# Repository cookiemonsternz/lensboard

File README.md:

# Lens Board

Lens Board is a custom mechanical keyboard, with a modified 1800's layout, more physical input methods (sliders, scrolly wheel, touchscreen) and an inbuilt, *physical* audio visualizer.

#### The Why

My inspiration for this project was my [Hackpad](https://hackpad.hackclub.com/) project, which I had a ton of fun designing and building. I wanted to make another thing to do with keyboards, and this was a great opportunity to do so.

In terms of the actual design choices of the keyboard, I'm a massive fan of analog / physical inputs and outputs. As a musician and LD, I like faders, so a few of those were an obvious choice. 

I decided to add a music visualizer because its just something I'm passionate about, putting some form of visual representation to sound. I do lighting for this reason, and I made my [music visualizer](https://cookiemonsternz.github.io/music-visualiser/) for high seas also because of this.

Anyways, here are some shots of my project :)

## BOM

For a nicer formatted bom, visit this [google sheet](https://docs.google.com/spreadsheets/d/1ZwZEnQPNZCf3j8q_c9diwTeRiC4rXLwVUGGG0oGG0jM/edit).

### Daughterboard

 Item | Part Name | Quantity | Source | Link | Unit Cost | Total Cost | Notes 
---|---|---|---|---|---|---|---
 U1 | RP2040 | 1 | JLCPCB Parts | https://jlcpcb.com/partdetail/RaspberryPi-RP2040/C2040 | 1.12 | 1.12 |  
 U2 | Voltage Regulator | 1 | JLCPCB Parts | https://jlcpcb.com/partdetail/bl_shanghai_belling-BL111733CX/C5400 | 0.05 | 0.05 | You can also use C26537, but its a bit more expensive 
 U3 | Flash Mem. | 1 | JLCPCB Parts | https://jlcpcb.com/partdetail/WinbondElec-W25Q128JVSIQ/C97521 | 0.74 | 0.74 |  
 U4 | Crystal Oscillator | 1 | JLCPCB Parts | https://jlcpcb.com/partdetail/AbraconLlc-ABM8_272T3/C20625731 | 0.36 | 0.36 |  
 U5, U6 | IO Expander | 2 | JLCPCB Parts | https://jlcpcb.com/partdetail/MicrochipTech-MCP23017T_EML/C629439 | 1.55 | 3.1 |  
 J1 | DC Barrel Jack | 1 | JLCPCB Parts | https://jlcpcb.com/partdetail/ShouHan-DC005/C431533 | 0.05 | 0.05 |  
 J2 | USB C Conn | 1 | JLCPCB Parts | https://jlcpcb.com/partdetail/Korean_HropartsElec-TYPE_C_31_M12/C165948 | 0.17 | 0.17 |  
 J3 | 2x30 Pin Header | 1 | Aliexpress | https://www.aliexpress.com/item/32214180690.html?spm=a2g0o.productlist.main.11.62007aa28osNlK&algo_pvid=4aeb8a1d-9196-4dce-9fd8-8f74cdbfb503&algo_exp_id=4aeb8a1d-9196-4dce-9fd8-8f74cdbfb503-10&pdp_ext_f=%7B%22order%22%3A%2212%22%2C%22eval%22%3A%221%22%7D&pdp_npi=4%40dis%21USD%210.76%210.76%21%21%210.76%210.76%21%402103246617503783498077610ef0cd%2112000023678787662%21sea%21NZ%212895682434%21X&curPageLogUid=gqU9QpHzRo8G&utparam-url=scene%3Asearch%7Cquery_from%3A | 0.15 | 0.15 |  
 R1, R2 | 1kΩ Resistor | 2 | JLCPCB Parts | https://jlcpcb.com/partdetail/12256-0402WGF1001TCE/C11702 | 0.01 | 0.02 |  
 R3, R4 | 27.4Ω Resistor | 2 | JLCPCB Parts | https://jlcpcb.com/partdetail/25848-0402WGF330JTCE/C25105 | 0.01 | 0.02 | Using 33Ω resistors instead here, technically not to spec, but will almost certainly still work 
 R5, R6 | 5.1kΩ Resistor | 2 | JLCPCB Parts | https://jlcpcb.com/partdetail/26648-0402WGF5101TCE/C25905 | 0.01 | 0.02 |  
 R7, R8 | 4.7kΩ Resistor | 2 | JLCPCB Parts | https://jlcpcb.com/partdetail/26643-0402WGF4701TCE/C25900 | 0.01 | 0.02 |  
 C1, C2 | 10uF Capacitor | 2 | JLCPCB Parts | https://jlcpcb.com/partdetail/20411-CL10A106KP8NNNC/C19702 | 0.01 | 0.02 | 0603, all other smd r and c are 0402 
 C3, C4, C5, C6, C7, C8, C9, C12, C13, C14 | 100nF Capacitor | 10 | JLCPCB Parts | https://jlcpcb.com/partdetail/1877-CL05B104KO5NNNC/C1525 | 0.01 | 0.1 |  
 C10, C11 | 1uF Capacitor | 2 | JLCPCB Parts | https://jlcpcb.com/partdetail/16531-CL10A105KB8NNNC/C15849 | 0.01 | 0.02 | 0603, all other smd r and c are 0402 
 C15, C16 | 15pF Capacitor | 2 | JLCPCB Parts | https://jlcpcb.com/partdetail/1900-0402CG150J500NT/C1548 | 0.01 | 0.02 |  
 BOARD | PCB Board | 1 | JLCPCB | NA | 0.8 | 0.8 | Excl. PCBA, default settings (1.6mm fr4), this is assuming 5 ordered, and this is the cost of 1 
 PCBA | PCB Assembly |  |  |  | 21.01 | 21.01 | This includes the cost of parts, so the cost of jlcpcb parts has been excluded from the total cost, again this is the cost for 1, but min order is 2 
 Total Cost |  |  |  |  |  |  |  
 Single Board |  |  |  |  |  | 21.96 |  
 Min Order (JLCPCB) |  |  |  |  |  | 46.17 |  

### Main Board

 Item | Part Name | Quantity | Source | Link | Unit Cost | Total Cost | Notes 
---|---|---|---|---|---|---|---
 BOARD | PCB Board | 1 | JLCPCB | NA | 5.38 | 5.38 | default settings (1.6mm fr4), this is assuming 5 ordered, and this is the cost of 1 
 J1 | 2x30 Pin Header | 1 | Aliexpress | https://www.aliexpress.com/item/32214180690.html?spm=a2g0o.productlist.main.11.62007aa28osNlK&algo_pvid=4aeb8a1d-9196-4dce-9fd8-8f74cdbfb503&algo_exp_id=4aeb8a1d-9196-4dce-9fd8-8f74cdbfb503-10&pdp_ext_f=%7B%22order%22%3A%2212%22%2C%22eval%22%3A%221%22%7D&pdp_npi=4%40dis%21USD%210.76%210.76%21%21%210.76%210.76%21%402103246617503783498077610ef0cd%2112000023678787662%21sea%21NZ%212895682434%21X&curPageLogUid=gqU9QpHzRo8G&utparam-url=scene%3Asearch%7Cquery_from%3A | 0.15 | 0.15 |  
 R109, R110 | Slide Potentiometer | 2 | Mouser | https://nz.mouser.com/ProductDetail/Bourns/PTA3043-2010CIB103?qs=QARuOjD9jaF0iQfIvhCxcQ%3D%3D | 1.4 | 2.8 | This is a hard part to find on aliexpress, I'm going to adapt my pcb to the ones I currently have, but be very careful how you choose this part 
 U7 | LED Transistor | 1 | Aliexpress | https://www.aliexpress.com/item/32966478417.html | 0.04 | 0.81 | Again, find one with the same footprint and similar specs 
 SW101 | Rotary Encoder | 1 | Aliexpress | https://www.aliexpress.com/item/1005008562951299.html?spm=a2g0o.productlist.main.2.694610473NnPbb&algo_pvid=771bf3ee-44f4-41f8-acc5-89f292c9e139&algo_exp_id=771bf3ee-44f4-41f8-acc5-89f292c9e139-1&pdp_ext_f=%7B%22order%22%3A%22-1%22%2C%22eval%22%3A%221%22%7D&pdp_npi=4%40dis%21USD%213.08%212.74%21%21%2122.00%2119.58%21%402103146c17504851750608347e0951%2112000045732012789%21sea%21NZ%212895682434%21X&curPageLogUid=0EsiDwbyuniA&utparam-url=scene%3Asearch%7Cquery_from%3A | 0.27 | 2.74 | Same as above 
 SW1 - SW 100 | Keyswitches | 100 | Aliexpress | https://www.aliexpress.com/item/1005009054805658.html | 0.23 | 22.81 | Assuming ordering 100 
 D1 - D100 | Key Diodes | 100 | Aliexpress | https://www.aliexpress.com/item/1005005460442161.html | 0.01 | 0.61 | Assuming ordering 100 
 D101 - D200 | Backlight LEDs | 100 | Aliexpress | https://www.aliexpress.com/item/1005005226854182.html | 0.01 | 1.45 | Assuming ordering 100 
 R9 - R108 | LED Resistor | 100 | Aliexpress | https://www.aliexpress.com/item/1005003297851656.html | 0.02 | 1.7 | Assuming ordering 100 
 J3, J4 | Touchscreen | 1 | Aliexpress | https://www.aliexpress.com/item/1005004055677573.html | 6.95 | 6.95 | With touch 
 M1 - M10 | Servo | 10 | Aliexpress | https://www.aliexpress.com/item/1005008626768357.html | 1.8 | 18.29 | 10x 180° MG90s 
 Total Cost |  |  |  |  |  |  |  
 Single Board |  |  |  |  |  | 63.69 |  
 Min Order (JLCPCB) |  |  |  |  |  | 103.11 | Only min order for jlcpcb, not for j1, all others already are min order. 

### Full Keyboard

 Item | Part Name | Quantity | Source | Link | Unit Cost | Total Cost | Notes 
---|---|---|---|---|---|---|---
 MAIN | Main Board | 1 | Various | NA | 81.59 | 103.11 | Total cost is different because of minimum orders 
 SUB | Daughter Board | 1 | Various | NA | 21.96 | 46.17 | Same as above, see individual boms 
 CASEB |  | 1 | 3d printing | NA | NA | NA | 3d printing this myself, not enough filament to compensate 
 CASET |  | 1 | 3d printing | NA | NA | NA | 3d printing this myself, not enough filament to compensate 
 PLATE |  | 1 | Laser cut / cnc | NA | NA | NA | 3d printing this myself, not enough filament to compensate 
 INS | Heatset inserts | 100 | Aliexpress | https://www.aliexpress.com/item/1005006838108683.html | 0.03 | 2.72 | OD 3.2, L3, M2, This is for 100, but couldn't find any smaller amounts 
 STA | Standoffs | 20 | Aliexpress | https://www.aliexpress.com/item/1005002952338852.html | 0.13 | 2.69 | M2, 12mm, 20 pc 
 KC | Keycaps | 100 | Aliexpress | https://www.aliexpress.com/item/1005008486798694.html | 0.05 | 5.44 |  
 Total Cost |  |  |  |  |  |  |  
 Single Board |  |  |  |  |  | 114.4 |  
 Total Cost (excl. Shipping) |  |  |  |  |  | 160.13 |  
 Total Cost (incl. Shipping) |  |  |  |  |  | 168.94 | Aliexpress parts = 70.60, JLCPCB = 98.34

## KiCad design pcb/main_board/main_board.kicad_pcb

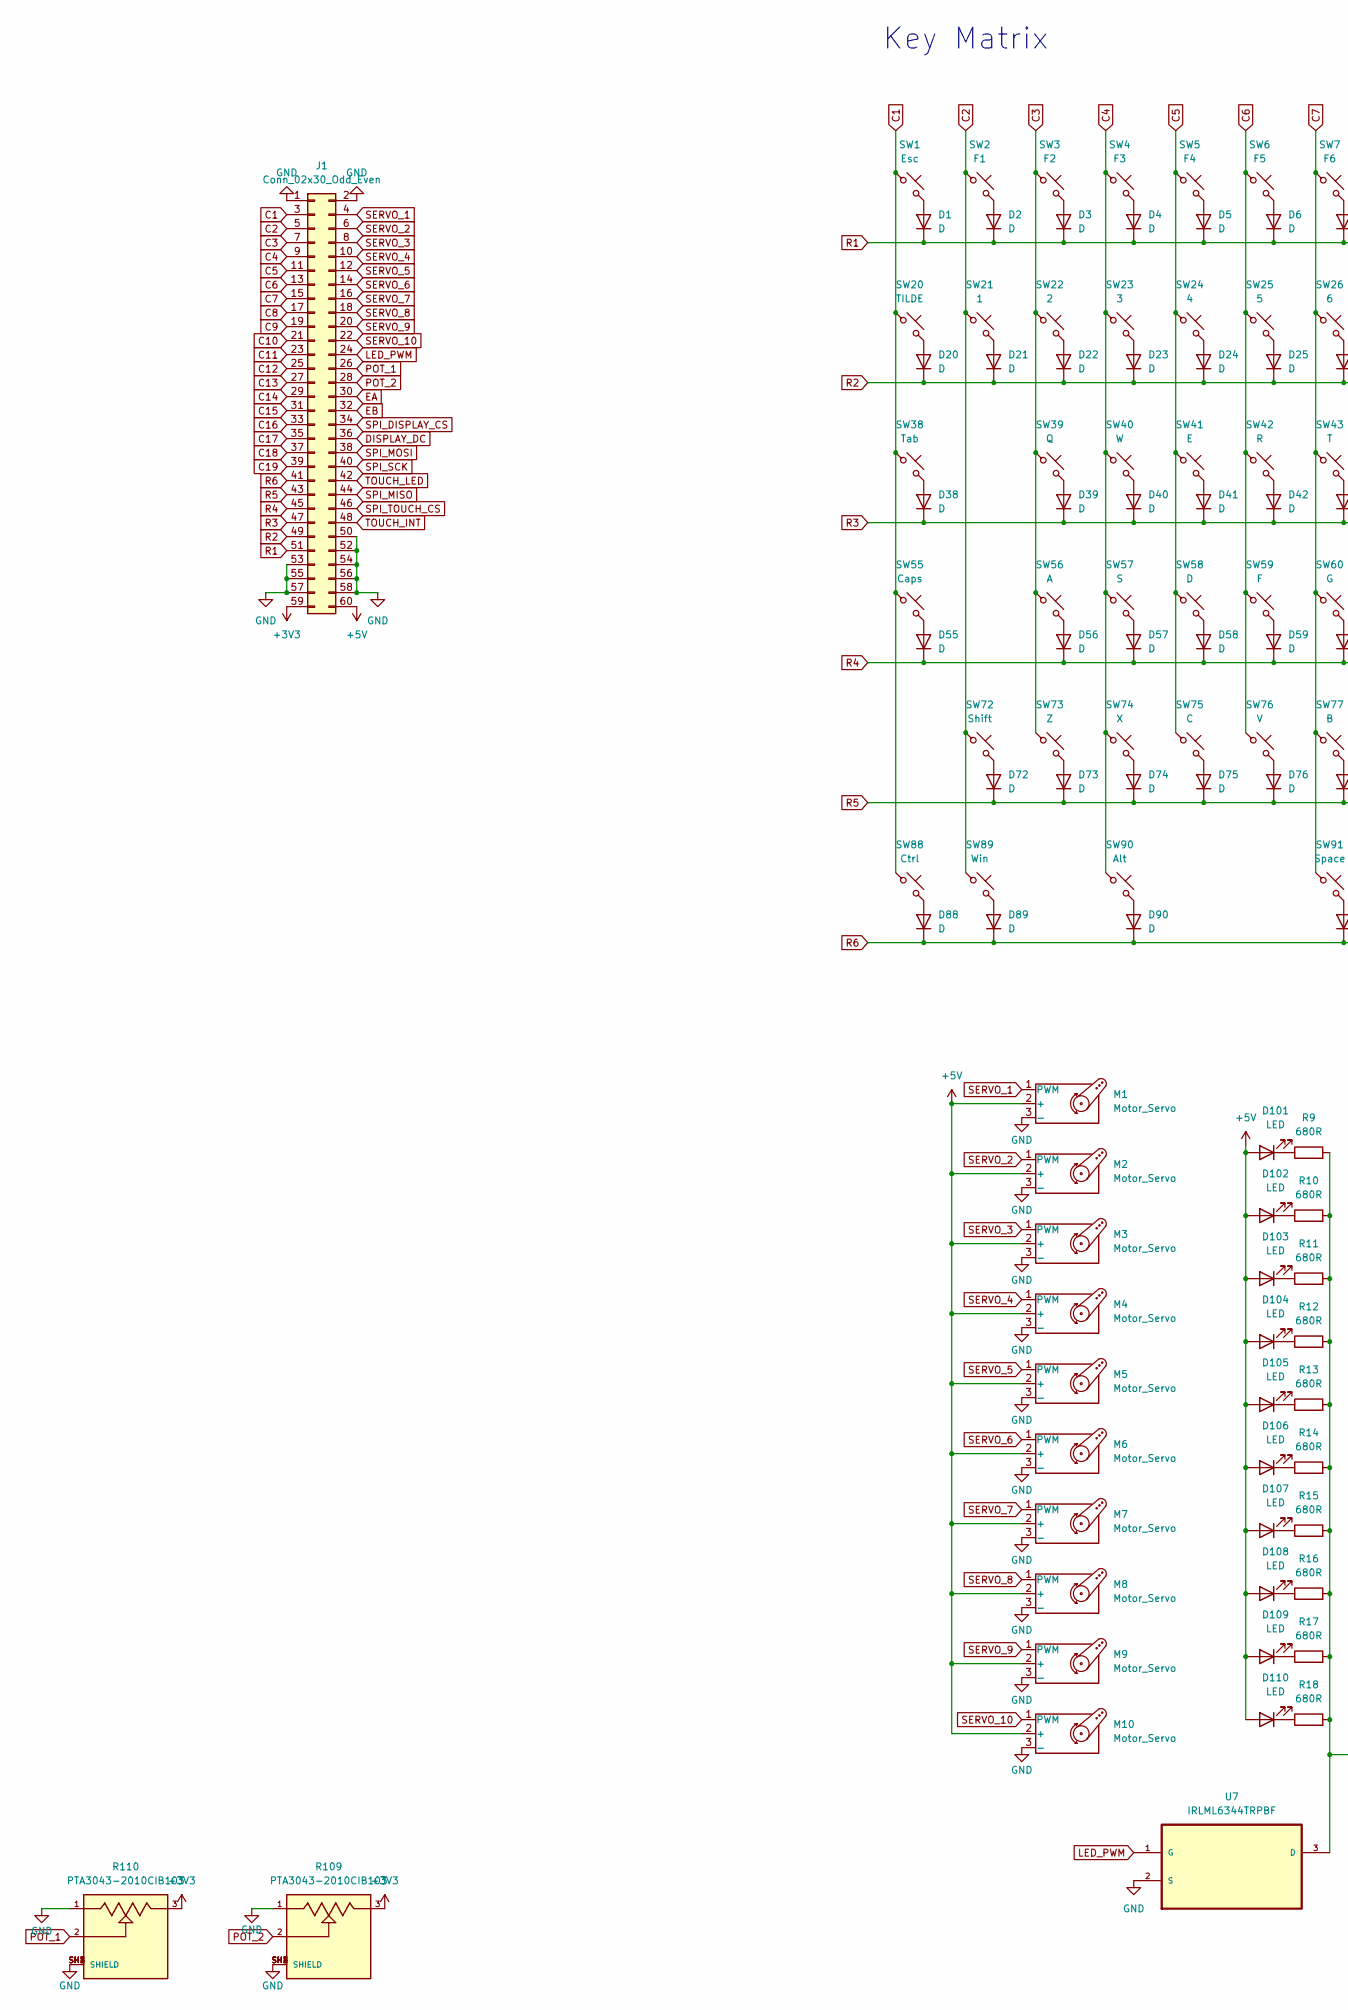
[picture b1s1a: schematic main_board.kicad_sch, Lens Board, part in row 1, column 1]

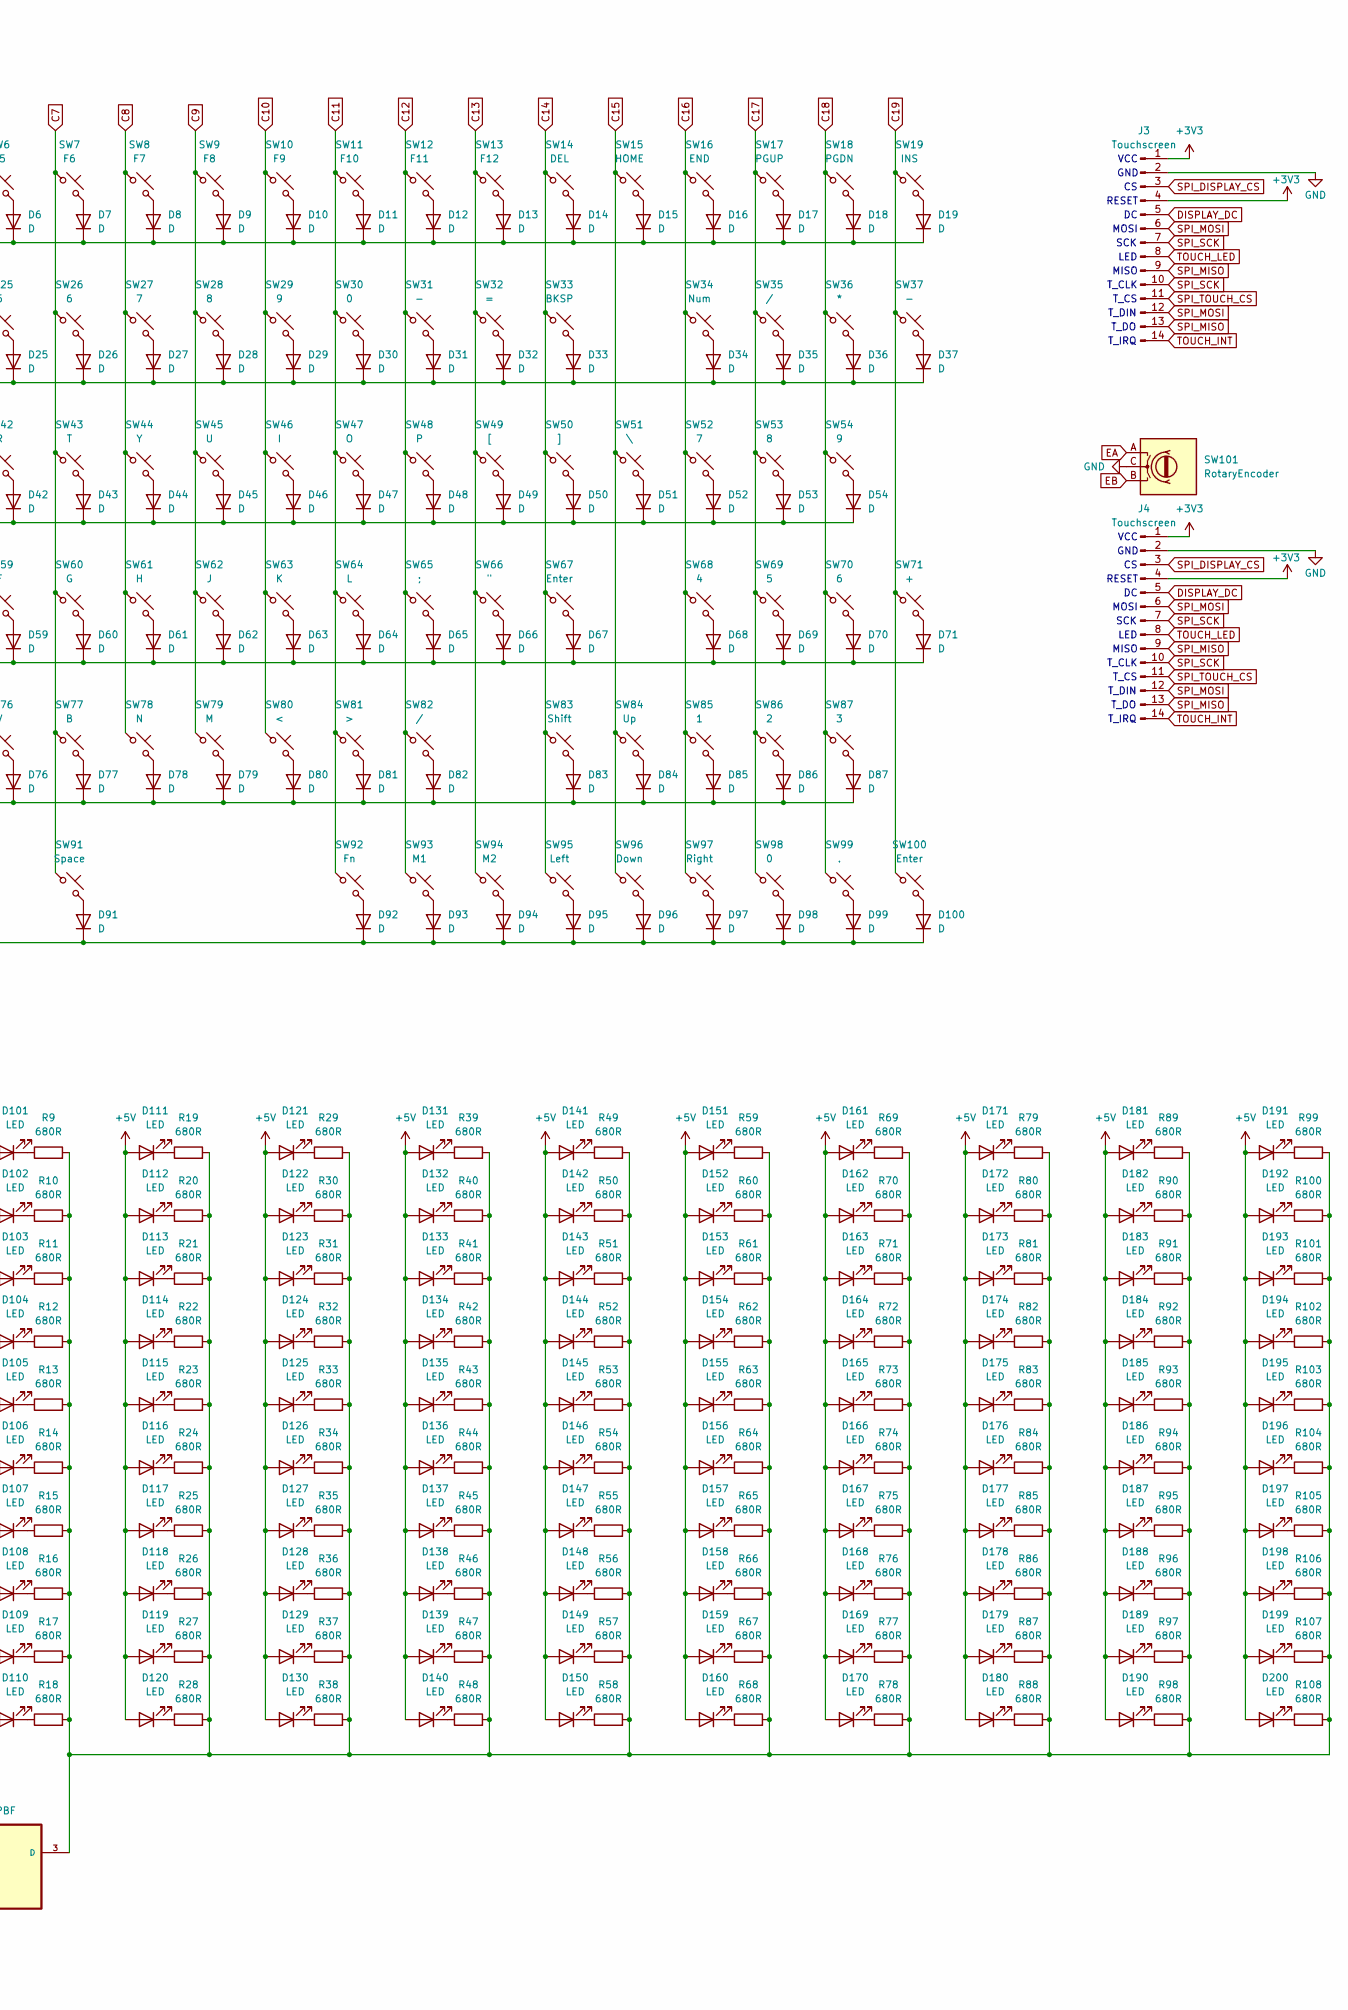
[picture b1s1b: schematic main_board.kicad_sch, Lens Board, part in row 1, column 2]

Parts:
D1, D2, D3, D4, D5, D6, D7, D8, D9, D10, D11, D12, D13, D14, D15, D16, D17, D18, D19, D20, D21, D22, D23, D24, D25, D26, D27, D28, D29, D30, D31, D32, D33, D34, D35, D36, D37, D38, D39, D40, D41, D42, D43, D44, D45, D46, D47, D48, D49, D50, D51, D52, D53, D54, D55, D56, D57, D58, D59, D60, D61, D62, D63, D64, D65, D66, D67, D68, D69, D70, D71, D72, D73, D74, D75, D76, D77, D78, D79, D80, D81, D82, D83, D84, D85, D86, D87, D88, D89, D90, D91, D92, D93, D94, D95, D96, D97, D98, D99, D100: D; D_SOD-323
D101, D102, D103, D104, D105, D106, D107, D108, D109, D110, D111, D112, D113, D114, D115, D116, D117, D118, D119, D120, D121, D122, D123, D124, D125, D126, D127, D128, D129, D130, D131, D132, D133, D134, D135, D136, D137, D138, D139, D140, D141, D142, D143, D144, D145, D146, D147, D148, D149, D150, D151, D152, D153, D154, D155, D156, D157, D158, D159, D160, D161, D162, D163, D164, D165, D166, D167, D168, D169, D170, D171, D172, D173, D174, D175, D176, D177, D178, D179, D180, D181, D182, D183, D184, D185, D186, D187, D188, D189, D190, D191, D192, D193, D194, D195, D196, D197, D198, D199, D200: LED; LED_0603_1608Metric
J1: Conn_02x30_Odd_Even; PinHeader_2x30_P1.27mm_Vertical
J3, J4: Touchscreen; PinHeader_1x14_P2.54mm_Vertical
M1, M2, M3, M4, M5, M6, M7, M8, M9, M10: Motor_Servo; PinHeader_1x03_P2.54mm_Vertical
R9, R10, R11, R12, R13, R14, R15, R16, R17, R18, R19, R20, R21, R22, R23, R24, R25, R26, R27, R28, R29, R30, R31, R32, R33, R34, R35, R36, R37, R38, R39, R40, R41, R42, R43, R44, R45, R46, R47, R48, R49, R50, R51, R52, R53, R54, R55, R56, R57, R58, R59, R60, R61, R62, R63, R64, R65, R66, R67, R68, R69, R70, R71, R72, R73, R74, R75, R76, R77, R78, R79, R80, R81, R82, R83, R84, R85, R86, R87, R88, R89, R90, R91, R92, R93, R94, R95, R96, R97, R98, R99, R100, R101, R102, R103, R104, R105, R106, R107, R108: 680R; R_0402_1005Metric
R109, R110: PTA3043-2010CIB103; TRIM_PTA3043-2010CIB103; PARTREV 04/21; DigiKey_Part_Number PTA3043-2010CIB103-ND
SW1: Esc; MX-Hotswap-1U
SW2: F1; MX-Hotswap-1U
SW3: F2; MX-Hotswap-1U
SW4: F3; MX-Hotswap-1U
SW5: F4; MX-Hotswap-1U
SW6: F5; MX-Hotswap-1U
SW7: F6; MX-Hotswap-1U
SW8: F7; MX-Hotswap-1U
SW9: F8; MX-Hotswap-1U
SW10: F9; MX-Hotswap-1U
SW11: F10; MX-Hotswap-1U
SW12: F11; MX-Hotswap-1U
SW13: F12; MX-Hotswap-1U
SW14: DEL; MX-Hotswap-1U
SW15: HOME; MX-Hotswap-1U
SW16: END; MX-Hotswap-1U
SW17: PGUP; MX-Hotswap-1U
SW18: PGDN; MX-Hotswap-1U
SW19: INS; MX-Hotswap-1U
SW20: TILDE; MX-Hotswap-1U
SW21, SW85: 1; MX-Hotswap-1U
SW22, SW86: 2; MX-Hotswap-1U
SW23, SW87: 3; MX-Hotswap-1U
SW24, SW68: 4; MX-Hotswap-1U
SW25, SW69: 5; MX-Hotswap-1U
SW26, SW70: 6; MX-Hotswap-1U
SW27, SW52: 7; MX-Hotswap-1U
SW28, SW53: 8; MX-Hotswap-1U
SW29, SW54: 9; MX-Hotswap-1U
SW30, SW98: 0; MX-Hotswap-1U
SW31, SW37: -; MX-Hotswap-1U
SW32: =; MX-Hotswap-1U
SW33: BKSP; MX-Hotswap-2U
SW34: Num; MX-Hotswap-1U
SW35, SW82: /; MX-Hotswap-1U
SW36: *; MX-Hotswap-1U
SW38: Tab; MX-Hotswap-1.5U
SW39: Q; MX-Hotswap-1U
SW40: W; MX-Hotswap-1U
SW41: E; MX-Hotswap-1U
SW42: R; MX-Hotswap-1U
SW43: T; MX-Hotswap-1U
SW44: Y; MX-Hotswap-1U
SW45: U; MX-Hotswap-1U
SW46: I; MX-Hotswap-1U
SW47: O; MX-Hotswap-1U
SW48: P; MX-Hotswap-1U
SW49: [; MX-Hotswap-1U
SW50: ]; MX-Hotswap-1U
SW51: \; MX-Hotswap-1.5U
SW55: Caps; MX-Hotswap-1.75U
SW56: A; MX-Hotswap-1U
SW57: S; MX-Hotswap-1U
SW58: D; MX-Hotswap-1U
SW59: F; MX-Hotswap-1U
SW60: G; MX-Hotswap-1U
SW61: H; MX-Hotswap-1U
SW62: J; MX-Hotswap-1U
SW63: K; MX-Hotswap-1U
SW64: L; MX-Hotswap-1U
SW65: ;; MX-Hotswap-1U
SW66: "; MX-Hotswap-1U
SW67: Enter; MX-Hotswap-2.25U
SW71: +; MX-Hotswap-2U-Vertical
SW72: Shift; MX-Hotswap-2.25U
SW73: Z; MX-Hotswap-1U
SW74: X; MX-Hotswap-1U
SW75: C; MX-Hotswap-1U
SW76: V; MX-Hotswap-1U
SW77: B; MX-Hotswap-1U
SW78: N; MX-Hotswap-1U
SW79: M; MX-Hotswap-1U
SW80: <; MX-Hotswap-1U
SW81: >; MX-Hotswap-1U
SW83: Shift; MX-Hotswap-1.75U
SW84: Up; MX-Hotswap-1U
SW88: Ctrl; MX-Hotswap-1.25U
SW89: Win; MX-Hotswap-1.25U
SW90: Alt; MX-Hotswap-1.25U
SW91: Space; MX-Hotswap-6.25U
SW92: Fn; MX-Hotswap-1U
SW93: M1; MX-Hotswap-1U
SW94: M2; MX-Hotswap-1U
SW95: Left; MX-Hotswap-1U
SW96: Down; MX-Hotswap-1U
SW97: Right; MX-Hotswap-1U
SW99: .; MX-Hotswap-1U
SW100: Enter; MX-Hotswap-2U-Vertical
SW101: RotaryEncoder; TRIM_EC10E1220501
U7: IRLML6344TRPBF; SOT95P240X112-3N; MPN IRLML6344TRPBF

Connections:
+3V3: J1.59, J3.1, J3.4, J4.1, J4.4, R109.3, R110.3
+5V: D101.2 (A), D102.2 (A), D103.2 (A), D104.2 (A), D105.2 (A), D106.2 (A), D107.2 (A), D108.2 (A), D109.2 (A), D110.2 (A), D111.2 (A), D112.2 (A), D113.2 (A), D114.2 (A), D115.2 (A), D116.2 (A), D117.2 (A), D118.2 (A), D119.2 (A), D120.2 (A), D121.2 (A), D122.2 (A), D123.2 (A), D124.2 (A), D125.2 (A), D126.2 (A), D127.2 (A), D128.2 (A), D129.2 (A), D130.2 (A), D131.2 (A), D132.2 (A), D133.2 (A), D134.2 (A), D135.2 (A), D136.2 (A), D137.2 (A), D138.2 (A), D139.2 (A), D140.2 (A), D141.2 (A), D142.2 (A), D143.2 (A), D144.2 (A), D145.2 (A), D146.2 (A), D147.2 (A), D148.2 (A), D149.2 (A), D150.2 (A), D151.2 (A), D152.2 (A), D153.2 (A), D154.2 (A), D155.2 (A), D156.2 (A), D157.2 (A), D158.2 (A), D159.2 (A), D160.2 (A), D161.2 (A), D162.2 (A), D163.2 (A), D164.2 (A), D165.2 (A), D166.2 (A), D167.2 (A), D168.2 (A), D169.2 (A), D170.2 (A), D171.2 (A), D172.2 (A), D173.2 (A), D174.2 (A), D175.2 (A), D176.2 (A), D177.2 (A), D178.2 (A), D179.2 (A), D180.2 (A), D181.2 (A), D182.2 (A), D183.2 (A), D184.2 (A), D185.2 (A), D186.2 (A), D187.2 (A), D188.2 (A), D189.2 (A), D190.2 (A), D191.2 (A), D192.2 (A), D193.2 (A), D194.2 (A), D195.2 (A), D196.2 (A), D197.2 (A), D198.2 (A), D199.2 (A), D200.2 (A), J1.60, M1.2 (+), M2.2 (+), M3.2 (+), M4.2 (+), M5.2 (+), M6.2 (+), M7.2 (+), M8.2 (+), M9.2 (+), M10.2 (+)
C1: J1.3, SW1.1, SW20.1, SW38.1, SW55.1, SW88.1
C2: J1.5, SW2.1, SW21.1, SW72.1, SW89.1
C3: J1.7, SW3.1, SW22.1, SW39.1, SW56.1, SW73.1
C4: J1.9, SW4.1, SW23.1, SW40.1, SW57.1, SW74.1, SW90.1
C5: J1.11, SW5.1, SW24.1, SW41.1, SW58.1, SW75.1
C6: J1.13, SW6.1, SW25.1, SW42.1, SW59.1, SW76.1
C7: J1.15, SW7.1, SW26.1, SW43.1, SW60.1, SW77.1, SW91.1
C8: J1.17, SW8.1, SW27.1, SW44.1, SW61.1, SW78.1
C9: J1.19, SW9.1, SW28.1, SW45.1, SW62.1, SW79.1
C10: J1.21, SW10.1, SW29.1, SW46.1, SW63.1, SW80.1
C11: J1.23, SW11.1, SW30.1, SW47.1, SW64.1, SW81.1, SW92.1
C12: J1.25, SW12.1, SW31.1, SW48.1, SW65.1, SW82.1, SW93.1
C13: J1.27, SW13.1, SW32.1, SW49.1, SW66.1, SW94.1
C14: J1.29, SW14.1, SW33.1, SW50.1, SW67.1, SW83.1, SW95.1
C15: J1.31, SW15.1, SW51.1, SW84.1, SW96.1
C16: J1.33, SW16.1, SW34.1, SW52.1, SW68.1, SW85.1, SW97.1
C17: J1.35, SW17.1, SW35.1, SW53.1, SW69.1, SW86.1, SW98.1
C18: J1.37, SW18.1, SW36.1, SW54.1, SW70.1, SW87.1, SW99.1
C19: J1.39, SW19.1, SW37.1, SW71.1, SW100.1
DISPLAY_DC: J1.36, J3.5, J4.5
EA: J1.30, SW101.A
EB: J1.32, SW101.B
GND: J1.1, J1.2, J1.50, J1.52, J1.53, J1.54, J1.55, J1.56, J1.57, J1.58, J3.2, J4.2, M1.3 (-), M2.3 (-), M3.3 (-), M4.3 (-), M5.3 (-), M6.3 (-), M7.3 (-), M8.3 (-), M9.3 (-), M10.3 (-), R109.1, R109.SH1 (SHIELD), R109.SH2 (SHIELD), R109.SH3 (SHIELD), R109.SH4 (SHIELD), R110.1, R110.SH1 (SHIELD), R110.SH2 (SHIELD), R110.SH3 (SHIELD), R110.SH4 (SHIELD), SW101.C, U7.2 (S)
LED_PWM: J1.24, U7.1 (G)
unnamed: D1.2 (A), SW1.2
unnamed: D2.2 (A), SW2.2
unnamed: D3.2 (A), SW3.2
unnamed: D4.2 (A), SW4.2
unnamed: D5.2 (A), SW5.2
unnamed: D6.2 (A), SW6.2
unnamed: D7.2 (A), SW7.2
unnamed: D8.2 (A), SW8.2
unnamed: D9.2 (A), SW9.2
unnamed: D10.2 (A), SW10.2
unnamed: D11.2 (A), SW11.2
unnamed: D12.2 (A), SW12.2
unnamed: D13.2 (A), SW13.2
unnamed: D14.2 (A), SW14.2
unnamed: D15.2 (A), SW15.2
unnamed: D16.2 (A), SW16.2
unnamed: D17.2 (A), SW17.2
unnamed: D18.2 (A), SW18.2
unnamed: D19.2 (A), SW19.2
unnamed: D20.2 (A), SW20.2
unnamed: D21.2 (A), SW21.2
unnamed: D22.2 (A), SW22.2
unnamed: D23.2 (A), SW23.2
unnamed: D24.2 (A), SW24.2
unnamed: D25.2 (A), SW25.2
unnamed: D26.2 (A), SW26.2
unnamed: D27.2 (A), SW27.2
unnamed: D28.2 (A), SW28.2
unnamed: D29.2 (A), SW29.2
unnamed: D30.2 (A), SW30.2
unnamed: D31.2 (A), SW31.2
unnamed: D32.2 (A), SW32.2
unnamed: D33.2 (A), SW33.2
unnamed: D34.2 (A), SW34.2
unnamed: D35.2 (A), SW35.2
unnamed: D36.2 (A), SW36.2
unnamed: D37.2 (A), SW37.2
unnamed: D38.2 (A), SW38.2
unnamed: D39.2 (A), SW39.2
unnamed: D40.2 (A), SW40.2
unnamed: D41.2 (A), SW41.2
unnamed: D42.2 (A), SW42.2
unnamed: D43.2 (A), SW43.2
unnamed: D44.2 (A), SW44.2
unnamed: D45.2 (A), SW45.2
unnamed: D46.2 (A), SW46.2
unnamed: D47.2 (A), SW47.2
unnamed: D48.2 (A), SW48.2
unnamed: D49.2 (A), SW49.2
unnamed: D50.2 (A), SW50.2
unnamed: D51.2 (A), SW51.2
unnamed: D52.2 (A), SW52.2
unnamed: D53.2 (A), SW53.2
unnamed: D54.2 (A), SW54.2
unnamed: D55.2 (A), SW55.2
unnamed: D56.2 (A), SW56.2
unnamed: D57.2 (A), SW57.2
unnamed: D58.2 (A), SW58.2
unnamed: D59.2 (A), SW59.2
unnamed: D60.2 (A), SW60.2
unnamed: D61.2 (A), SW61.2
unnamed: D62.2 (A), SW62.2
unnamed: D63.2 (A), SW63.2
unnamed: D64.2 (A), SW64.2
unnamed: D65.2 (A), SW65.2
unnamed: D66.2 (A), SW66.2
unnamed: D67.2 (A), SW67.2
unnamed: D68.2 (A), SW68.2
unnamed: D69.2 (A), SW69.2
unnamed: D70.2 (A), SW70.2
unnamed: D71.2 (A), SW71.2
unnamed: D72.2 (A), SW72.2
unnamed: D73.2 (A), SW73.2
unnamed: D74.2 (A), SW74.2
unnamed: D75.2 (A), SW75.2
unnamed: D76.2 (A), SW76.2
unnamed: D77.2 (A), SW77.2
unnamed: D78.2 (A), SW78.2
unnamed: D79.2 (A), SW79.2
unnamed: D80.2 (A), SW80.2
unnamed: D81.2 (A), SW81.2
unnamed: D82.2 (A), SW82.2
unnamed: D83.2 (A), SW83.2
unnamed: D84.2 (A), SW84.2
unnamed: D85.2 (A), SW85.2
unnamed: D86.2 (A), SW86.2
unnamed: D87.2 (A), SW87.2
unnamed: D88.2 (A), SW88.2
unnamed: D89.2 (A), SW89.2
unnamed: D90.2 (A), SW90.2
unnamed: D91.2 (A), SW91.2
unnamed: D92.2 (A), SW92.2
unnamed: D93.2 (A), SW93.2
unnamed: D94.2 (A), SW94.2
unnamed: D95.2 (A), SW95.2
unnamed: D96.2 (A), SW96.2
unnamed: D97.2 (A), SW97.2
unnamed: D98.2 (A), SW98.2
unnamed: D99.2 (A), SW99.2
unnamed: D100.2 (A), SW100.2
unnamed: D101.1 (K), R9.1
unnamed: D102.1 (K), R10.1
unnamed: D103.1 (K), R11.1
unnamed: D104.1 (K), R12.1
unnamed: D105.1 (K), R13.1
unnamed: D106.1 (K), R14.1
unnamed: D107.1 (K), R15.1
unnamed: D108.1 (K), R16.1
unnamed: D109.1 (K), R17.1
unnamed: D110.1 (K), R18.1
unnamed: D111.1 (K), R19.1
unnamed: D112.1 (K), R20.1
unnamed: D113.1 (K), R21.1
unnamed: D114.1 (K), R22.1
unnamed: D115.1 (K), R23.1
unnamed: D116.1 (K), R24.1
unnamed: D117.1 (K), R25.1
unnamed: D118.1 (K), R26.1
unnamed: D119.1 (K), R27.1
unnamed: D120.1 (K), R28.1
unnamed: D121.1 (K), R29.1
unnamed: D122.1 (K), R30.1
unnamed: D123.1 (K), R31.1
unnamed: D124.1 (K), R32.1
unnamed: D125.1 (K), R33.1
unnamed: D126.1 (K), R34.1
unnamed: D127.1 (K), R35.1
unnamed: D128.1 (K), R36.1
unnamed: D129.1 (K), R37.1
unnamed: D130.1 (K), R38.1
unnamed: D131.1 (K), R39.1
unnamed: D132.1 (K), R40.1
unnamed: D133.1 (K), R41.1
unnamed: D134.1 (K), R42.1
unnamed: D135.1 (K), R43.1
unnamed: D136.1 (K), R44.1
unnamed: D137.1 (K), R45.1
unnamed: D138.1 (K), R46.1
unnamed: D139.1 (K), R47.1
unnamed: D140.1 (K), R48.1
unnamed: D141.1 (K), R49.1
unnamed: D142.1 (K), R50.1
unnamed: D143.1 (K), R51.1
unnamed: D144.1 (K), R52.1
unnamed: D145.1 (K), R53.1
unnamed: D146.1 (K), R54.1
unnamed: D147.1 (K), R55.1
unnamed: D148.1 (K), R56.1
unnamed: D149.1 (K), R57.1
unnamed: D150.1 (K), R58.1
unnamed: D151.1 (K), R59.1
unnamed: D152.1 (K), R60.1
unnamed: D153.1 (K), R61.1
unnamed: D154.1 (K), R62.1
unnamed: D155.1 (K), R63.1
unnamed: D156.1 (K), R64.1
unnamed: D157.1 (K), R65.1
unnamed: D158.1 (K), R66.1
unnamed: D159.1 (K), R67.1
unnamed: D160.1 (K), R68.1
unnamed: D161.1 (K), R69.1
unnamed: D162.1 (K), R70.1
unnamed: D163.1 (K), R71.1
unnamed: D164.1 (K), R72.1
unnamed: D165.1 (K), R73.1
unnamed: D166.1 (K), R74.1
unnamed: D167.1 (K), R75.1
unnamed: D168.1 (K), R76.1
unnamed: D169.1 (K), R77.1
unnamed: D170.1 (K), R78.1
unnamed: D171.1 (K), R79.1
unnamed: D172.1 (K), R80.1
unnamed: D173.1 (K), R81.1
unnamed: D174.1 (K), R82.1
unnamed: D175.1 (K), R83.1
unnamed: D176.1 (K), R84.1
unnamed: D177.1 (K), R85.1
unnamed: D178.1 (K), R86.1
unnamed: D179.1 (K), R87.1
unnamed: D180.1 (K), R88.1
unnamed: D181.1 (K), R89.1
unnamed: D182.1 (K), R90.1
unnamed: D183.1 (K), R91.1
unnamed: D184.1 (K), R92.1
unnamed: D185.1 (K), R93.1
unnamed: D186.1 (K), R94.1
unnamed: D187.1 (K), R95.1
unnamed: D188.1 (K), R96.1
unnamed: D189.1 (K), R97.1
unnamed: D190.1 (K), R98.1
unnamed: D191.1 (K), R99.1
unnamed: D192.1 (K), R100.1
unnamed: D193.1 (K), R101.1
unnamed: D194.1 (K), R102.1
unnamed: D195.1 (K), R103.1
unnamed: D196.1 (K), R104.1
unnamed: D197.1 (K), R105.1
unnamed: D198.1 (K), R106.1
unnamed: D199.1 (K), R107.1
unnamed: D200.1 (K), R108.1
unnamed: R9.2, R10.2, R11.2, R12.2, R13.2, R14.2, R15.2, R16.2, R17.2, R18.2, R19.2, R20.2, R21.2, R22.2, R23.2, R24.2, R25.2, R26.2, R27.2, R28.2, R29.2, R30.2, R31.2, R32.2, R33.2, R34.2, R35.2, R36.2, R37.2, R38.2, R39.2, R40.2, R41.2, R42.2, R43.2, R44.2, R45.2, R46.2, R47.2, R48.2, R49.2, R50.2, R51.2, R52.2, R53.2, R54.2, R55.2, R56.2, R57.2, R58.2, R59.2, R60.2, R61.2, R62.2, R63.2, R64.2, R65.2, R66.2, R67.2, R68.2, R69.2, R70.2, R71.2, R72.2, R73.2, R74.2, R75.2, R76.2, R77.2, R78.2, R79.2, R80.2, R81.2, R82.2, R83.2, R84.2, R85.2, R86.2, R87.2, R88.2, R89.2, R90.2, R91.2, R92.2, R93.2, R94.2, R95.2, R96.2, R97.2, R98.2, R99.2, R100.2, R101.2, R102.2, R103.2, R104.2, R105.2, R106.2, R107.2, R108.2, U7.3 (D)
POT_1: J1.26, R110.2
POT_2: J1.28, R109.2
R1: D1.1 (K), D2.1 (K), D3.1 (K), D4.1 (K), D5.1 (K), D6.1 (K), D7.1 (K), D8.1 (K), D9.1 (K), D10.1 (K), D11.1 (K), D12.1 (K), D13.1 (K), D14.1 (K), D15.1 (K), D16.1 (K), D17.1 (K), D18.1 (K), D19.1 (K), J1.51
R2: D20.1 (K), D21.1 (K), D22.1 (K), D23.1 (K), D24.1 (K), D25.1 (K), D26.1 (K), D27.1 (K), D28.1 (K), D29.1 (K), D30.1 (K), D31.1 (K), D32.1 (K), D33.1 (K), D34.1 (K), D35.1 (K), D36.1 (K), D37.1 (K), J1.49
R3: D38.1 (K), D39.1 (K), D40.1 (K), D41.1 (K), D42.1 (K), D43.1 (K), D44.1 (K), D45.1 (K), D46.1 (K), D47.1 (K), D48.1 (K), D49.1 (K), D50.1 (K), D51.1 (K), D52.1 (K), D53.1 (K), D54.1 (K), J1.47
R4: D55.1 (K), D56.1 (K), D57.1 (K), D58.1 (K), D59.1 (K), D60.1 (K), D61.1 (K), D62.1 (K), D63.1 (K), D64.1 (K), D65.1 (K), D66.1 (K), D67.1 (K), D68.1 (K), D69.1 (K), D70.1 (K), D71.1 (K), J1.45
R5: D72.1 (K), D73.1 (K), D74.1 (K), D75.1 (K), D76.1 (K), D77.1 (K), D78.1 (K), D79.1 (K), D80.1 (K), D81.1 (K), D82.1 (K), D83.1 (K), D84.1 (K), D85.1 (K), D86.1 (K), D87.1 (K), J1.43
R6: D88.1 (K), D89.1 (K), D90.1 (K), D91.1 (K), D92.1 (K), D93.1 (K), D94.1 (K), D95.1 (K), D96.1 (K), D97.1 (K), D98.1 (K), D99.1 (K), D100.1 (K), J1.41
SERVO_1: J1.4, M1.1 (PWM)
SERVO_2: J1.6, M2.1 (PWM)
SERVO_3: J1.8, M3.1 (PWM)
SERVO_4: J1.10, M4.1 (PWM)
SERVO_5: J1.12, M5.1 (PWM)
SERVO_6: J1.14, M6.1 (PWM)
SERVO_7: J1.16, M7.1 (PWM)
SERVO_8: J1.18, M8.1 (PWM)
SERVO_9: J1.20, M9.1 (PWM)
SERVO_10: J1.22, M10.1 (PWM)
SPI_DISPLAY_CS: J1.34, J3.3, J4.3
SPI_MISO: J1.44, J3.9, J3.13, J4.9, J4.13
SPI_MOSI: J1.38, J3.6, J3.12, J4.6, J4.12
SPI_SCK: J1.40, J3.7, J3.10, J4.7, J4.10
SPI_TOUCH_CS: J1.46, J3.11, J4.11
TOUCH_INT: J1.48, J3.14, J4.14
TOUCH_LED: J1.42, J3.8, J4.8

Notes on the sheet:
MISO
GND
T_IRQ
T_CS
T_CLK
VCC
MOSI
T_DO
LED
RESET
SCK
Key Matrix
T_DIN

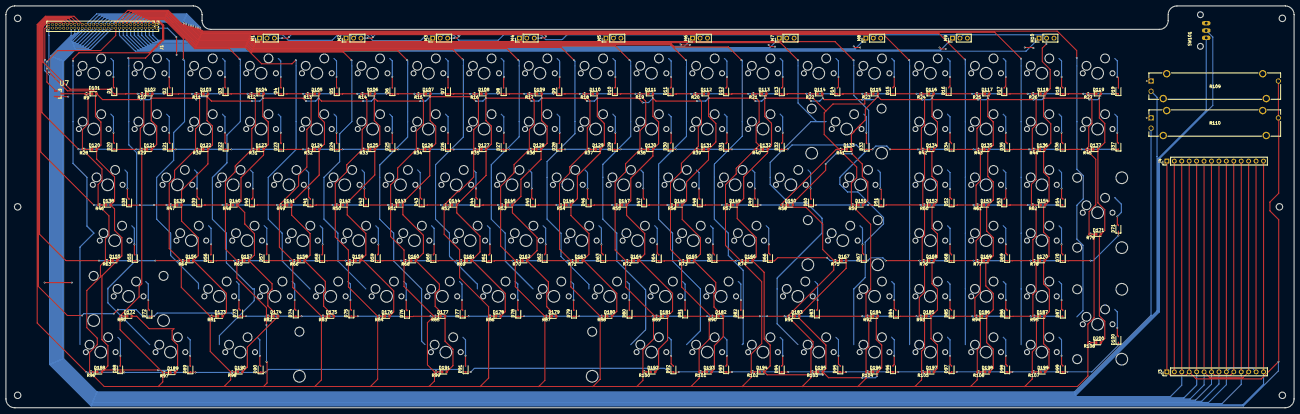
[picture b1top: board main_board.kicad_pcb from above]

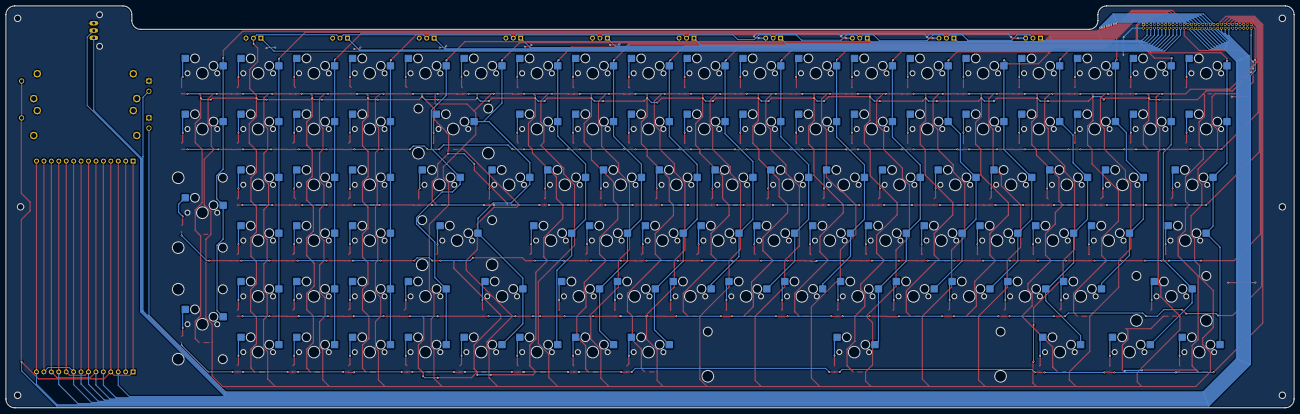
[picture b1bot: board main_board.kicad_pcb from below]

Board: 2 copper layers, 440.0 x 137.2 mm, 417 parts (100 on the bottom side), 252 nets.

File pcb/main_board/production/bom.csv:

Designator,Footprint,Quantity,Value,LCSC Part #
"D1, D10, D100, D11, D12, D13, D14, D15, D16, D17, D18, D19, D2, D20, D21, D22, D23, D24, D25, D26, D27, D28, D29, D3, D30, D31, D32, D33, D34, D35, D36, D37, D38, D39, D4, D40, D41, D42, D43, D44, D45, D46, D47, D48, D49, D5, D50, D51, D52, D53, D54, D55, D56, D57, D58, D59, D6, D60, D61, D62, D63, D64, D65, D66, D67, D68, D69, D7, D70, D71, D72, D73, D74, D75, D76, D77, D78, D79, D8, D80, D81, D82, D83, D84, D85, D86, D87, D88, D89, D9, D90, D91, D92, D93, D94, D95, D96, D97, D98, D99",D_SOD-323,100,D,
"D101, D102, D103, D104, D105, D106, D107, D108, D109, D110, D111, D112, D113, D114, D115, D116, D117, D118, D119, D120, D121, D122, D123, D124, D125, D126, D127, D128, D129, D130, D131, D132, D133, D134, D135, D136, D137, D138, D139, D140, D141, D142, D143, D144, D145, D146, D147, D148, D149, D150, D151, D152, D153, D154, D155, D156, D157, D158, D159, D160, D161, D162, D163, D164, D165, D166, D167, D168, D169, D170, D171, D172, D173, D174, D175, D176, D177, D178, D179, D180, D181, D182, D183, D184, D185, D186, D187, D188, D189, D190, D191, D192, D193, D194, D195, D196, D197, D198, D199, D200",0603,100,LED,
J1,PinHeader_2x30_P1.27mm_Vertical,1,Conn_02x30_Odd_Even,
"J3, J4",PinHeader_1x14_P2.54mm_Vertical,2,Touchscreen,
"M1, M10, M2, M3, M4, M5, M6, M7, M8, M9",PinHeader_1x03_P2.54mm_Vertical,10,Motor_Servo,
"R10, R100, R101, R102, R103, R104, R105, R106, R107, R108, R11, R12, R13, R14, R15, R16, R17, R18, R19, R20, R21, R22, R23, R24, R25, R26, R27, R28, R29, R30, R31, R32, R33, R34, R35, R36, R37, R38, R39, R40, R41, R42, R43, R44, R45, R46, R47, R48, R49, R50, R51, R52, R53, R54, R55, R56, R57, R58, R59, R60, R61, R62, R63, R64, R65, R66, R67, R68, R69, R70, R71, R72, R73, R74, R75, R76, R77, R78, R79, R80, R81, R82, R83, R84, R85, R86, R87, R88, R89, R9, R90, R91, R92, R93, R94, R95, R96, R97, R98, R99",0402,100,680R,
"R109, R110",TRIM_PTA3043-2010CIB103,2,PTA3043-2010CIB103,
SW1,MX-Hotswap-1U,1,Esc,
SW10,MX-Hotswap-1U,1,F9,
SW100,MX-Hotswap-2U-Vertical,1,Enter,
SW101,TRIM_EC10E1220501,1,RotaryEncoder,
SW11,MX-Hotswap-1U,1,F10,
SW12,MX-Hotswap-1U,1,F11,
SW13,MX-Hotswap-1U,1,F12,
SW14,MX-Hotswap-1U,1,DEL,
SW15,MX-Hotswap-1U,1,HOME,
SW16,MX-Hotswap-1U,1,END,
SW17,MX-Hotswap-1U,1,PGUP,
SW18,MX-Hotswap-1U,1,PGDN,
SW19,MX-Hotswap-1U,1,INS,
SW2,MX-Hotswap-1U,1,F1,
SW20,MX-Hotswap-1U,1,TILDE,
"SW21, SW85",MX-Hotswap-1U,2,1,
"SW22, SW86",MX-Hotswap-1U,2,2,
"SW23, SW87",MX-Hotswap-1U,2,3,
"SW24, SW68",MX-Hotswap-1U,2,4,
"SW25, SW69",MX-Hotswap-1U,2,5,
"SW26, SW70",MX-Hotswap-1U,2,6,
"SW27, SW52",MX-Hotswap-1U,2,7,
"SW28, SW53",MX-Hotswap-1U,2,8,
"SW29, SW54",MX-Hotswap-1U,2,9,
SW3,MX-Hotswap-1U,1,F2,
"SW30, SW98",MX-Hotswap-1U,2,0,
"SW31, SW37",MX-Hotswap-1U,2,-,
SW32,MX-Hotswap-1U,1,=,
SW33,MX-Hotswap-2U,1,BKSP,
SW34,MX-Hotswap-1U,1,Num,
"SW35, SW82",MX-Hotswap-1U,2,/,
SW36,MX-Hotswap-1U,1,*,
SW38,MX-Hotswap-1.5U,1,Tab,
SW39,MX-Hotswap-1U,1,Q,
SW4,MX-Hotswap-1U,1,F3,
SW40,MX-Hotswap-1U,1,W,
SW41,MX-Hotswap-1U,1,E,
SW42,MX-Hotswap-1U,1,R,
SW43,MX-Hotswap-1U,1,T,
SW44,MX-Hotswap-1U,1,Y,
SW45,MX-Hotswap-1U,1,U,
SW46,MX-Hotswap-1U,1,I,
SW47,MX-Hotswap-1U,1,O,
SW48,MX-Hotswap-1U,1,P,
SW49,MX-Hotswap-1U,1,[,
SW5,MX-Hotswap-1U,1,F4,
SW50,MX-Hotswap-1U,1,],
SW51,MX-Hotswap-1.5U,1,\,
SW55,MX-Hotswap-1.75U,1,Caps,
SW56,MX-Hotswap-1U,1,A,
SW57,MX-Hotswap-1U,1,S,
SW58,MX-Hotswap-1U,1,D,
SW59,MX-Hotswap-1U,1,F,
SW6,MX-Hotswap-1U,1,F5,
SW60,MX-Hotswap-1U,1,G,
SW61,MX-Hotswap-1U,1,H,
SW62,MX-Hotswap-1U,1,J,
SW63,MX-Hotswap-1U,1,K,
SW64,MX-Hotswap-1U,1,L,
SW65,MX-Hotswap-1U,1,;,
SW66,MX-Hotswap-1U,1,"""",
SW67,MX-Hotswap-2.25U,1,Enter,
SW7,MX-Hotswap-1U,1,F6,
SW71,MX-Hotswap-2U-Vertical,1,+,
SW72,MX-Hotswap-2.25U,1,Shift,
SW73,MX-Hotswap-1U,1,Z,
SW74,MX-Hotswap-1U,1,X,
SW75,MX-Hotswap-1U,1,C,
SW76,MX-Hotswap-1U,1,V,
SW77,MX-Hotswap-1U,1,B,
SW78,MX-Hotswap-1U,1,N,
SW79,MX-Hotswap-1U,1,M,
SW8,MX-Hotswap-1U,1,F7,
SW80,MX-Hotswap-1U,1,<,
SW81,MX-Hotswap-1U,1,>,
SW83,MX-Hotswap-1.75U,1,Shift,
SW84,MX-Hotswap-1U,1,Up,
SW88,MX-Hotswap-1.25U,1,Ctrl,
SW89,MX-Hotswap-1.25U,1,Win,
SW9,MX-Hotswap-1U,1,F8,
SW90,MX-Hotswap-1.25U,1,Alt,
SW91,MX-Hotswap-6.25U,1,Space,
SW92,MX-Hotswap-1U,1,Fn,
SW93,MX-Hotswap-1U,1,M1,
SW94,MX-Hotswap-1U,1,M2,
SW95,MX-Hotswap-1U,1,Left,
SW96,MX-Hotswap-1U,1,Down,
SW97,MX-Hotswap-1U,1,Right,
SW99,MX-Hotswap-1U,1,.,
U7,SOT95P240X112-3N,1,IRLML6344TRPBF,IRLML6344TRPBF
